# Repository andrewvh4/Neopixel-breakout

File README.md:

# Neopixel-breakout
A simple breakout board for a NeoPixel LED strip

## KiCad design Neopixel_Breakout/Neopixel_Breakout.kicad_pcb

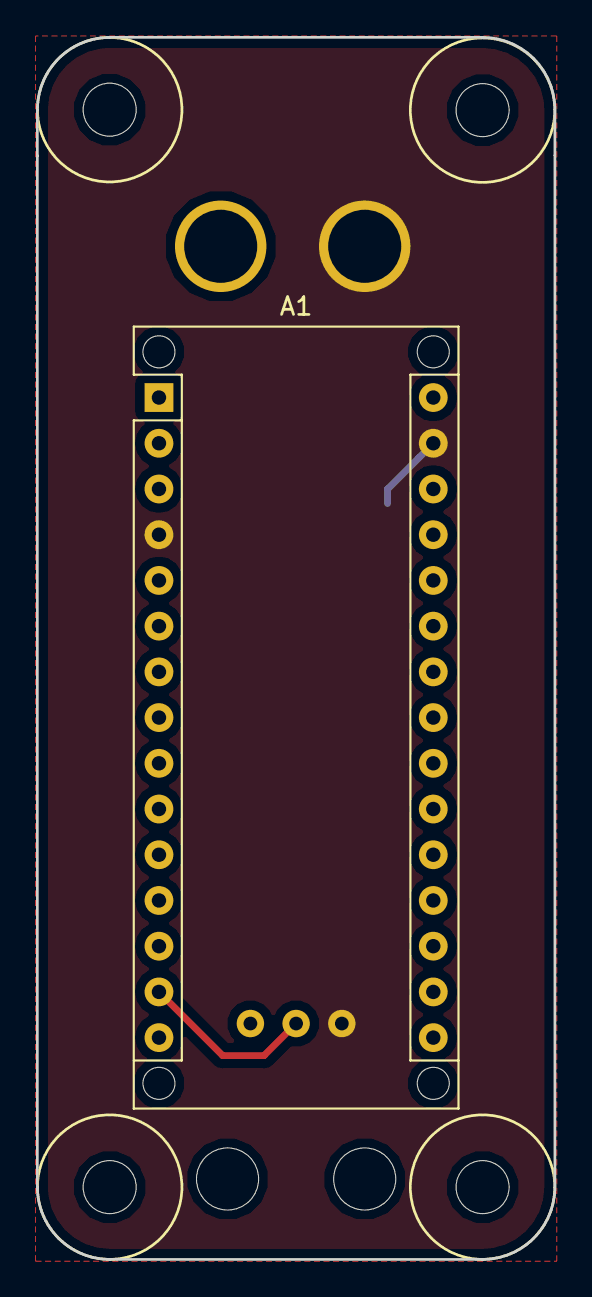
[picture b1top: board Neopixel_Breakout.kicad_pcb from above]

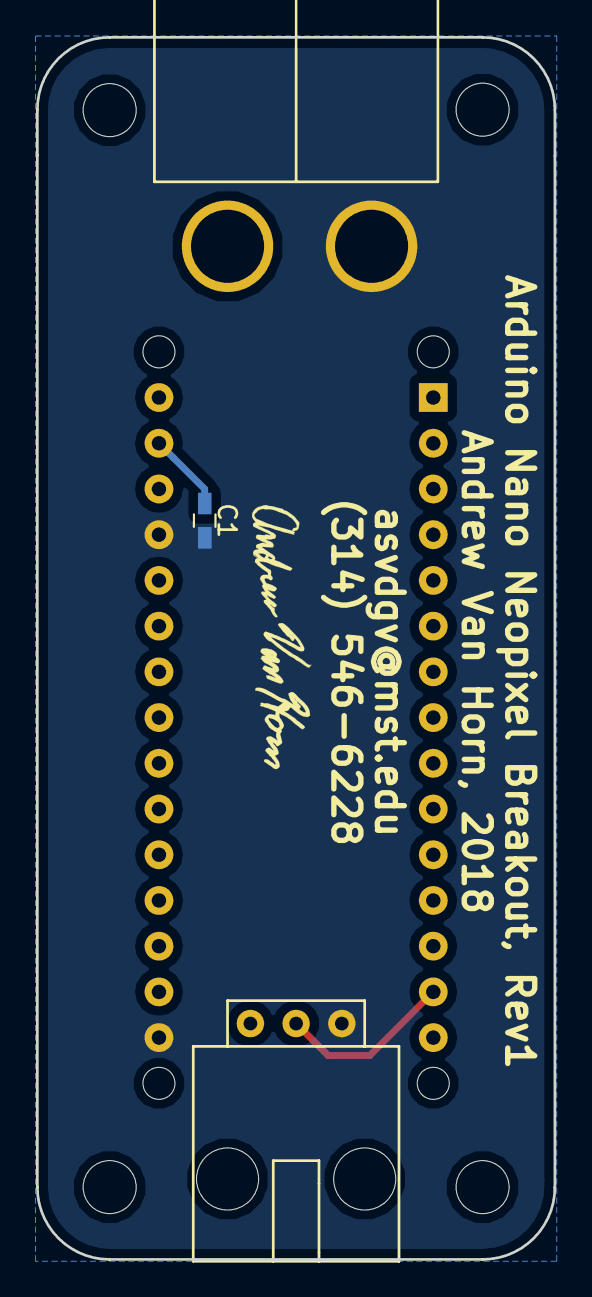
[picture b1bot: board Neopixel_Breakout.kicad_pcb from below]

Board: 2 copper layers, 28.8 x 67.9 mm, 4 parts (3 on the bottom side), 3 nets.

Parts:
A1: Arduino_Nano_v3.x; Arduino_Nano_WithMountingHoles
C1: 10u; C_0603_HandSoldering
Conn1: AndersonPP; Anderson_2_Horisontal_Side_by_Side
Conn2: Molex_SL_03; MOLEX_SL_03_Horizontal

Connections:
+5V: A1.16, A1.27, C1.2, Conn1.2, Conn2.1
GND: A1.4, A1.29, C1.1, Conn1.1, Conn2.3
Neo_Sig: A1.14, Conn2.2

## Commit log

2018-11-21 Created Project
